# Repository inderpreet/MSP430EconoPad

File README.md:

MSP430 G Series Econo Launchpad
===============================
This is the PCB design for the TI MSP430 Economy Launchpad. It fits in a 5cm x 5xm area and does not include the programmer. You can buy an official launchpad and then use this to make standalone Launchpads. This is NOT the official design but rather my version.

The project is at www.github.com/inderpreet/MSP430Econopad

Format is EagleCAD schematic and board layout

For more details, check out the website at

-----> http://embeddedcode.wordpress.com

## Support
I would love your support and currently I am not able accept any donations. Just give a shout out to me at www.twitter.com/ip_v1 and help with documentation of this project and I will be very thankful. Enjoy the board.

###Designed by Inderpreet Singh Of Guru Nanak Dev Univeristy, Amritsar

This software may be distributed and modified under the terms of the GNU
General Public License version 2 (GPL2) as published by the Free Software
Foundation and appearing in the file LICENSE.TXT included in the packaging of
this file. Please note that GPL2 Section 2[b] requires that all works based
on this software must also be made publicly available under the terms of
the GPL2 ("Copyleft").

We put a lot of time and effort into our project and hence this copyright 
notice ensures that people contribute as well as each contribution is 
acknowledged. Please retain this original notice and if you make changes
please document them below along with your details.

The latest copy of this project/library can be found at: 
https://github.com/inderpreet/

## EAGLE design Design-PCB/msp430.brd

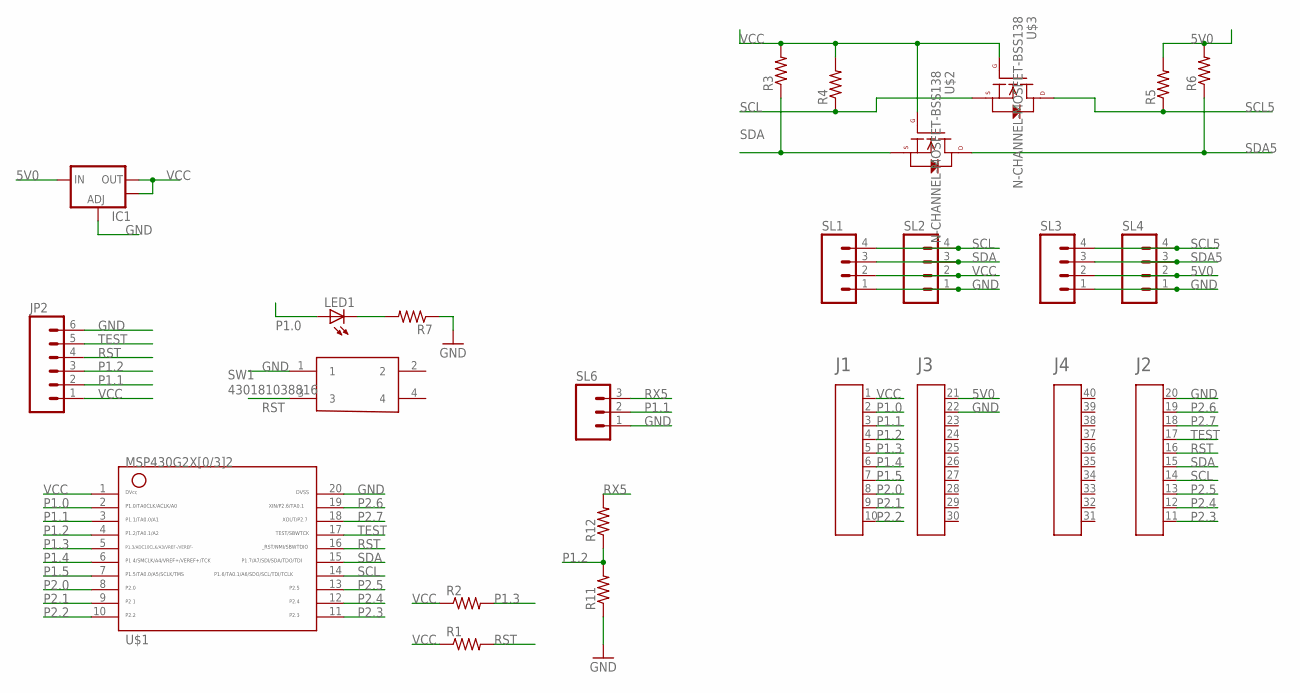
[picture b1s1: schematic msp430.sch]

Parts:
A1: HEADER4X10-BOOSTERPACK; 4X10-BOOSTERPACK
IC1: V_REG_LM1117SOT223; SOT223
JP2: M06LOCK; 1X06_LOCK
LED1: LEDCHIPLED_0805; CHIPLED_0805
R1, R2, R3, R4, R5, R6, R7, R11, R12: R-US_M0805; M0805
SL1, SL2, SL3, SL4: M04; 04P
SL6: M03; 03P
SW1: 430181038816
U$1: G2X[0/3]2---N20; N20
U$2, U$3: N-CHANNEL-MOSFET-BSS138; SOT23-3

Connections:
5V0: A1.21, IC1.3 (IN), R5.2, R6.2, SL3.2, SL4.2
GND: A1.20, A1.22, IC1.1 (ADJ), JP2.6, R7.1, R11.1, SL1.1, SL2.1, SL3.1, SL4.1, SL6.1, SW1.1, U$1.20
unnamed: LED1.C, R7.2
P1.0: A1.2, LED1.A, U$1.2
P1.1: A1.3, JP2.2, SL6.2, U$1.3
P1.2: A1.4, JP2.3, R11.2, R12.1, U$1.4
P1.3: A1.5, R2.2, U$1.5
P1.4: A1.6, U$1.6
P1.5: A1.7, U$1.7
P2.0: A1.8, U$1.8
P2.1: A1.9, U$1.9
P2.2: A1.10, U$1.10
P2.3: A1.11, U$1.11
P2.4: A1.12, U$1.12
P2.5: A1.13, U$1.13
P2.6: A1.19, U$1.19
P2.7: A1.18, U$1.18
RST: A1.16, JP2.4, R1.2, SW1.3, U$1.16
RX5: R12.2, SL6.3
SCL: A1.14, R4.1, SL1.4, SL2.4, U$1.14, U$3.2 (S)
SCL5: R5.1, SL3.4, SL4.4, U$3.3 (D)
SDA: A1.15, R3.1, SL1.3, SL2.3, U$1.15, U$2.2 (S)
SDA5: R6.1, SL3.3, SL4.3, U$2.3 (D)
TEST: A1.17, JP2.5, U$1.17
VCC: A1.1, IC1.2 (OUT), IC1.4 (OUT), JP2.1, R1.1, R2.1, R3.2, R4.2, SL1.2, SL2.2, U$1.1, U$2.1 (G), U$3.1 (G)

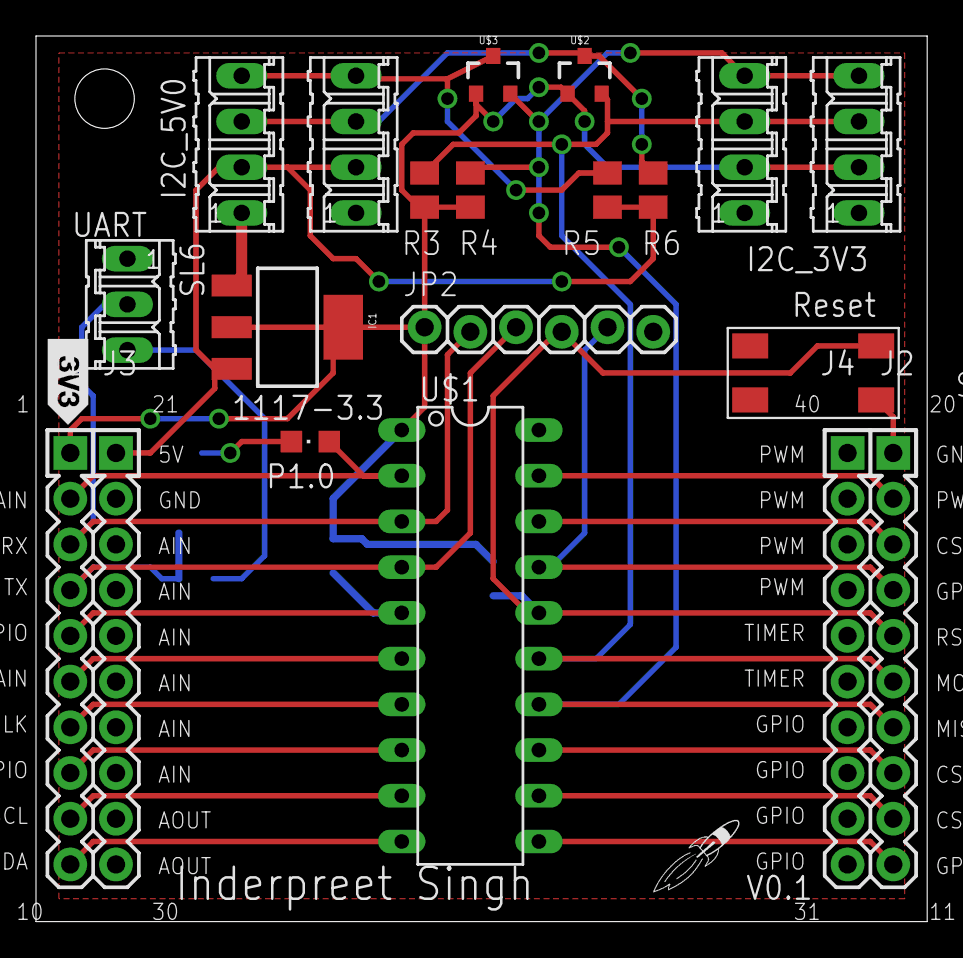
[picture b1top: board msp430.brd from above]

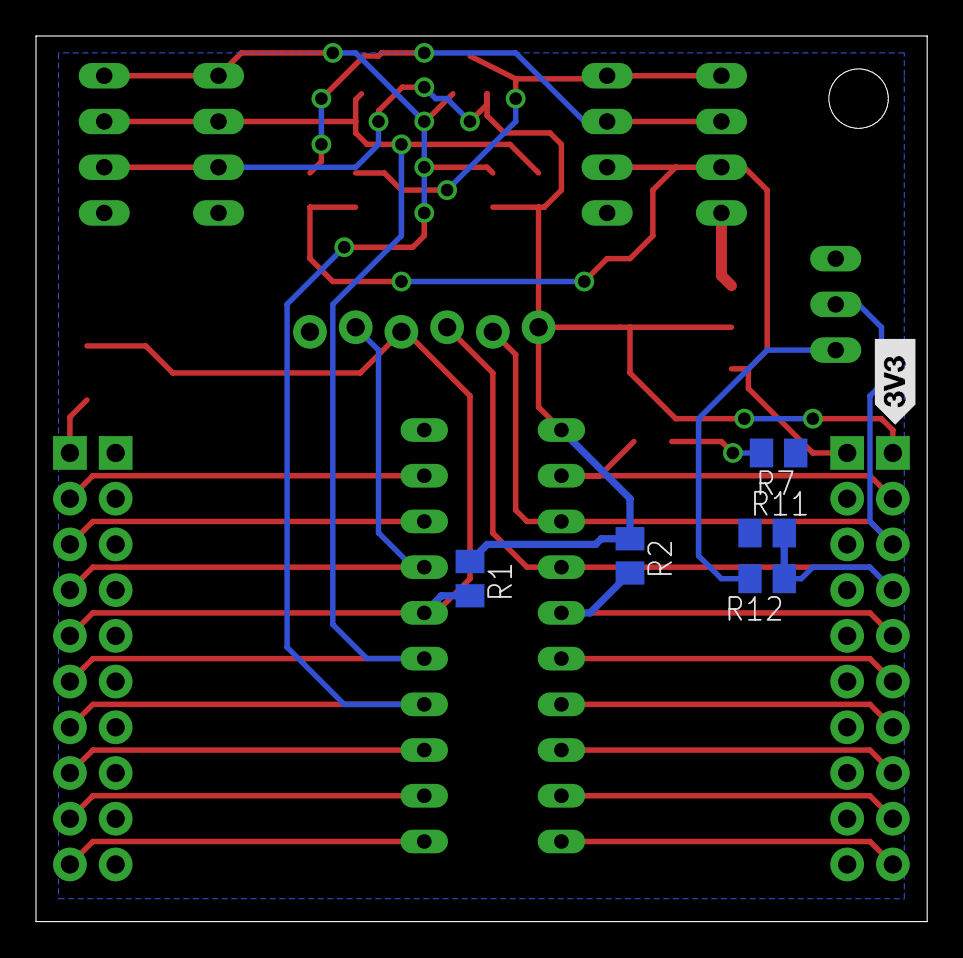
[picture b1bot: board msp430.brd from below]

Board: 2 copper layers, 49.5 x 49.2 mm, 25 parts (5 on the bottom side), 25 nets.

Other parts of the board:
U$4: STAND-OFF
U$5: SILK_3V3_TAG
U$6: LOGO-ROCKET

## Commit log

2016-03-17 First OK Version. Will be sent to fabrication

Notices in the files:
parts and their libraries:
SparkFun-Electromechanical: Licensing: Creative Commons ShareAlike 4.0 International - https://creativecommons.org/licenses/by-sa/4.0
